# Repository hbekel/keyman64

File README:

Keyman64

Programmable C64 keyboard interceptor and hardware control system

The keyman64 is a programmable keyboard interceptor and hardware
control system for computers equipped with a simple 64-key matrix
keyboard.

It is installed between the keyboard and the computer, continually
scanning the keyboard matrix and relaying the keyboard state to the
computer using a crosspoint switch. To the computer, the crosspoint
switch matrix looks just like a physical keyboard, while the keyman64
gains the ability to intercept keystrokes and control the matrix seen
by the computer.

The keyman64 can be configured to intercept special key combinations
and invoke arbitrary sequences of commands to alter the state of
sixteen general purpose control lines provided on the board. These
lines can be used to control additional hardware instead of using
physical buttons or switches.

Additional features include the ability to send predefined keyboard
macros or to redefine the keyboard layout. Commands can also be sent
from a remote PC via USB, or send on simple serial wire interface,
allowing remote control from either a PC or another microcontroller or
similar device.

For some concrete examples of what the keyman64 can do, see the

http://www.henning-bekel.de/keyman64/#configuration-examples

Please refer to the project page http://www.henning-bekel.de/keyman64
for detailed documentation.

Copyright 2016 Henning Bekel <h.bekel@googlemail.com>

LICENSING

Hardware licenced under CERN OHL v.1.2, see ./hardware/LICENSE.txt
Software and firmware licenced under GNU GPLv3, see ./LICENSE

The software contains MIT licensed code from
https://github.com/arkku/ihex for reading Intel HEX files, Copyright
(c) 2013-2015 Kimmo Kulovesi, see ./intelhex/LICENSE

The firmware contains the V-USB Driver (https://www.obdev.at/vusb),
(C)2008 Objective Development GmbH.

Distributed in the ./bootloader directory is the USBasp bootloader,
(C)2013 Stephan Baerwolf (matrixstorm@gmx.de) and (C)2008 Objective
Development GmbH (https://www.obdev.at/vusb).

In compliance with the terms of the (identical) V-USB driver and
USBasp bootloader licenses (./firmware/usbdrv/License.txt and
./bootloader/License.txt), the entire project is published under

http://www.henning-bekel.de/keyman64

In addition, this distribution contains

- a circuit diagram in PDF format, see ./hardware/keyman64-schematics.pdf
- the full source code for the host software in ./firmware
- this README file
- references to https://www.obdev.at/vusb

The USB Product and Vendor IDs for the Keyman64 USB device have kindly
been provided by OpenMoko, Inc (http://openmoko.org).

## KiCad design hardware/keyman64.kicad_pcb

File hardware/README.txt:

Keyman64 Rev.4 -- Keyboard interceptor and hardware controller
Copyright Henning Bekel 2016.
Licensed under CERN OSH v.1.2 (see LICENSE.pdf)

This directory contains hardware documentation (as defined by the
terms of the CERN OSH v.1.2) for the Keyman64, a programmable
keyboard interceptor and hardware controller for the Commodore
C64. For more information, please visit

http://www.henning-bekel.de/keyman64

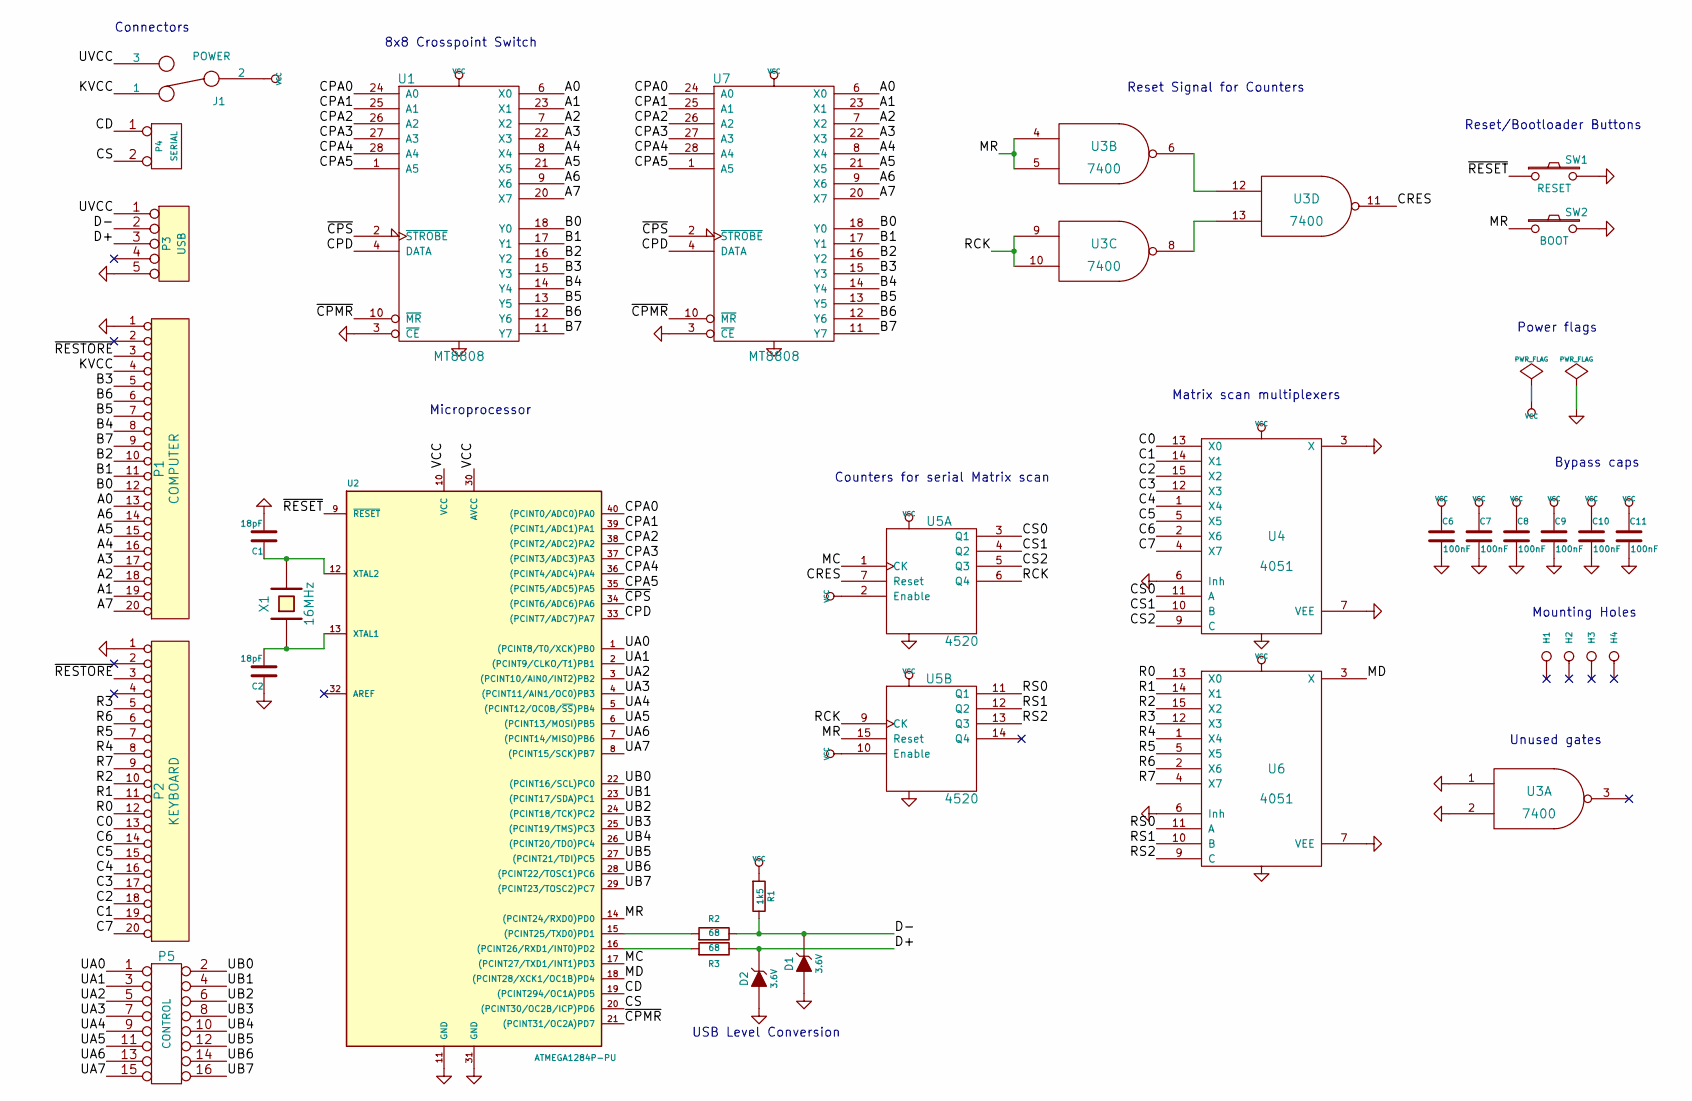
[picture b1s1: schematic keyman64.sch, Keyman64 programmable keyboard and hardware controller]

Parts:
C1, C2: 18pF; C_Disc_D3_P2.5
C6, C7, C8, C9, C10, C11: 100nF; C_Disc_D3_P2.5
D1, D2: 3.6V; D3
H1, H2, H3, H4: CONN_1; MountingHole_4mm
J1: POWER; pinHeader-3x1
P1: COMPUTER; pinHeader-20x1
P2: KEYBOARD; pinHeader-20x1
P3: USB; USB-MINI-B-H
P4: SERIAL; pinHeader-2x1
P5: CONTROL; pin_array_8x2
R1: 1k5; R3
R2, R3: 68; R3
SW1: RESET; Button
SW2: BOOT; Button
U1: MT8808; DIP-28__600
U2: ATMEGA1284P-PU; DIP-40__600
U3: 7400; DIP-14__300
U4, U6: 4051; DIP-16__300
U5: 4520; DIP-16__300
U7: MT8808; PLCC28
X1: 16MHz; HC-49V

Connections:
/A0: P1.13, U1.6 (X0), U7.6 (X0)
/A1: P1.19, U1.23 (X1), U7.23 (X1)
/A2: P1.18, U1.7 (X2), U7.7 (X2)
/A3: P1.17, U1.22 (X3), U7.22 (X3)
/A4: P1.16, U1.8 (X4), U7.8 (X4)
/A5: P1.15, U1.21 (X5), U7.21 (X5)
/A6: P1.14, U1.9 (X6), U7.9 (X6)
/A7: P1.20, U1.20 (X7), U7.20 (X7)
/B0: P1.12, U1.18 (Y0), U7.18 (Y0)
/B1: P1.11, U1.17 (Y1), U7.17 (Y1)
/B2: P1.10, U1.16 (Y2), U7.16 (Y2)
/B3: P1.5, U1.15 (Y3), U7.15 (Y3)
/B4: P1.8, U1.14 (Y4), U7.14 (Y4)
/B5: P1.7, U1.13 (Y5), U7.13 (Y5)
/B6: P1.6, U1.12 (Y6), U7.12 (Y6)
/B7: P1.9, U1.11 (Y7), U7.11 (Y7)
/C0: P2.13, U4.13 (X0)
/C1: P2.19, U4.14 (X1)
/C2: P2.18, U4.15 (X2)
/C3: P2.17, U4.12 (X3)
/C4: P2.16, U4.1 (X4)
/C5: P2.15, U4.5 (X5)
/C6: P2.14, U4.2 (X6)
/C7: P2.20, U4.4 (X7)
/CD: P4.1, U2.19 ((PCINT294/OC1A)PD5)
/CPA0: U1.24 (A0), U2.40 ((PCINT0/ADC0)PA0), U7.24 (A0)
/CPA1: U1.25 (A1), U2.39 ((PCINT1/ADC1)PA1), U7.25 (A1)
/CPA2: U1.26 (A2), U2.38 ((PCINT2/ADC2)PA2), U7.26 (A2)
/CPA3: U1.27 (A3), U2.37 ((PCINT3/ADC3)PA3), U7.27 (A3)
/CPA4: U1.28 (A4), U2.36 ((PCINT4/ADC4)PA4), U7.28 (A4)
/CPA5: U1.1 (A5), U2.35 ((PCINT5/ADC5)PA5), U7.1 (A5)
/CPD: U1.4 (DATA), U2.33 ((PCINT7/ADC7)PA7), U7.4 (DATA)
/CRES: U3.11, U5.7 (Reset)
/CS: P4.2 (PM), U2.20 ((PCINT30/OC2B/ICP)PD6)
/CS0: U4.11 (A), U5.3 (Q1)
/CS1: U4.10 (B), U5.4 (Q2)
/CS2: U4.9 (C), U5.5 (Q3)
/D+: D2.1 (K), P3.3, R3.1
/D-: D1.1 (K), P3.2, R1.1, R2.1
/KVCC: J1.1, P1.4
/MC: U2.17 ((PCINT27/TXD1/INT1)PD3), U5.1 (CK)
/MD: U2.18 ((PCINT28/XCK1/OC1B)PD4), U6.3 (X)
/MR: SW2.1, U2.14 ((PCINT24/RXD0)PD0), U3.4, U3.5, U5.15 (Reset)
/R0: P2.12, U6.13 (X0)
/R1: P2.11, U6.14 (X1)
/R2: P2.10, U6.15 (X2)
/R3: P2.5, U6.12 (X3)
/R4: P2.8, U6.1 (X4)
/R5: P2.7, U6.5 (X5)
/R6: P2.6, U6.2 (X6)
/R7: P2.9, U6.4 (X7)
/RCK: U3.9, U3.10, U5.6 (Q4), U5.9 (CK)
/RS0: U5.11 (Q1), U6.11 (A)
/RS1: U5.12 (Q2), U6.10 (B)
/RS2: U5.13 (Q3), U6.9 (C)
/UA0: P5.1, U2.1 ((PCINT8/T0/XCK)PB0)
/UA1: P5.3, U2.2 ((PCINT9/CLKO/T1)PB1)
/UA2: P5.5, U2.3 ((PCINT10/AIN0/INT2)PB2)
/UA3: P5.7, U2.4 ((PCINT11/AIN1/OC0)PB3)
/UA4: P5.9, U2.5 ((PCINT12/OC0B/~SS~)PB4)
/UA5: P5.11, U2.6 ((PCINT13/MOSI)PB5)
/UA6: P5.13, U2.7 ((PCINT14/MISO)PB6)
/UA7: P5.15, U2.8 ((PCINT15/SCK)PB7)
/UB0: P5.2, U2.22 ((PCINT16/SCL)PC0)
/UB1: P5.4, U2.23 ((PCINT17/SDA)PC1)
/UB2: P5.6, U2.24 ((PCINT18/TCK)PC2)
/UB3: P5.8, U2.25 ((PCINT19/TMS)PC3)
/UB4: P5.10, U2.26 ((PCINT20/TDO)PC4)
/UB5: P5.12, U2.27 ((PCINT21/TDI)PC5)
/UB6: P5.14, U2.28 ((PCINT22/TOSC1)PC6)
/UB7: P5.16, U2.29 ((PCINT23/TOSC2)PC7)
/UVCC: J1.3, P3.1
/~CPMR: U1.10 (~MR), U2.21 ((PCINT31/OC2A)PD7), U7.10 (~MR)
/~CPS: U1.2 (~STROBE), U2.34 ((PCINT6/ADC6)PA6), U7.2 (~STROBE)
/~RESET: SW1.1, U2.9 (~RESET)
/~RESTORE: P1.3, P2.3
GND: C1.2, C2.1, C6.2, C7.2, C8.2, C9.2, C10.2, C11.2, D1.2 (A), D2.2 (A), P1.1, P2.1, P3.5, SW1.2, SW2.2, U1.3 (~CE), U1.5 (VSS), U2.11 (GND), U2.31 (GND), U3.1, U3.2, U3.7 (GND), U4.3 (X), U4.6 (Inh), U4.7 (VEE), U4.8 (VSS), U5.8 (VSS), U6.6 (Inh), U6.7 (VEE), U6.8 (VSS), U7.3 (~CE), U7.5 (VSS)
unnamed: C1.1, U2.12 (XTAL2), X1.2
unnamed: C2.2, U2.13 (XTAL1), X1.1
unnamed: R2.2, U2.15 ((PCINT25/TXD0)PD1)
unnamed: R3.2, U2.16 ((PCINT26/RXD1/INT0)PD2)
unnamed: U3.6, U3.12
unnamed: U3.8, U3.13
VCC: C6.1, C7.1, C8.1, C9.1, C10.1, C11.1, J1.2, R1.2, U1.19 (VDD), U2.10 (VCC), U2.30 (AVCC), U3.14 (VCC), U4.16 (VDD), U5.2 (Enable), U5.10 (Enable), U5.16 (VDD), U6.16 (VDD), U7.19 (VDD)

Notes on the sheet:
USB Level Conversion
8x8 Crosspoint Switch
Reset Signal for Counters
Connectors
Counters for serial Matrix scan
Matrix scan multiplexers
Reset/Bootloader Buttons
Microprocessor
Unused gates
Power flags
Bypass caps
Mounting Holes

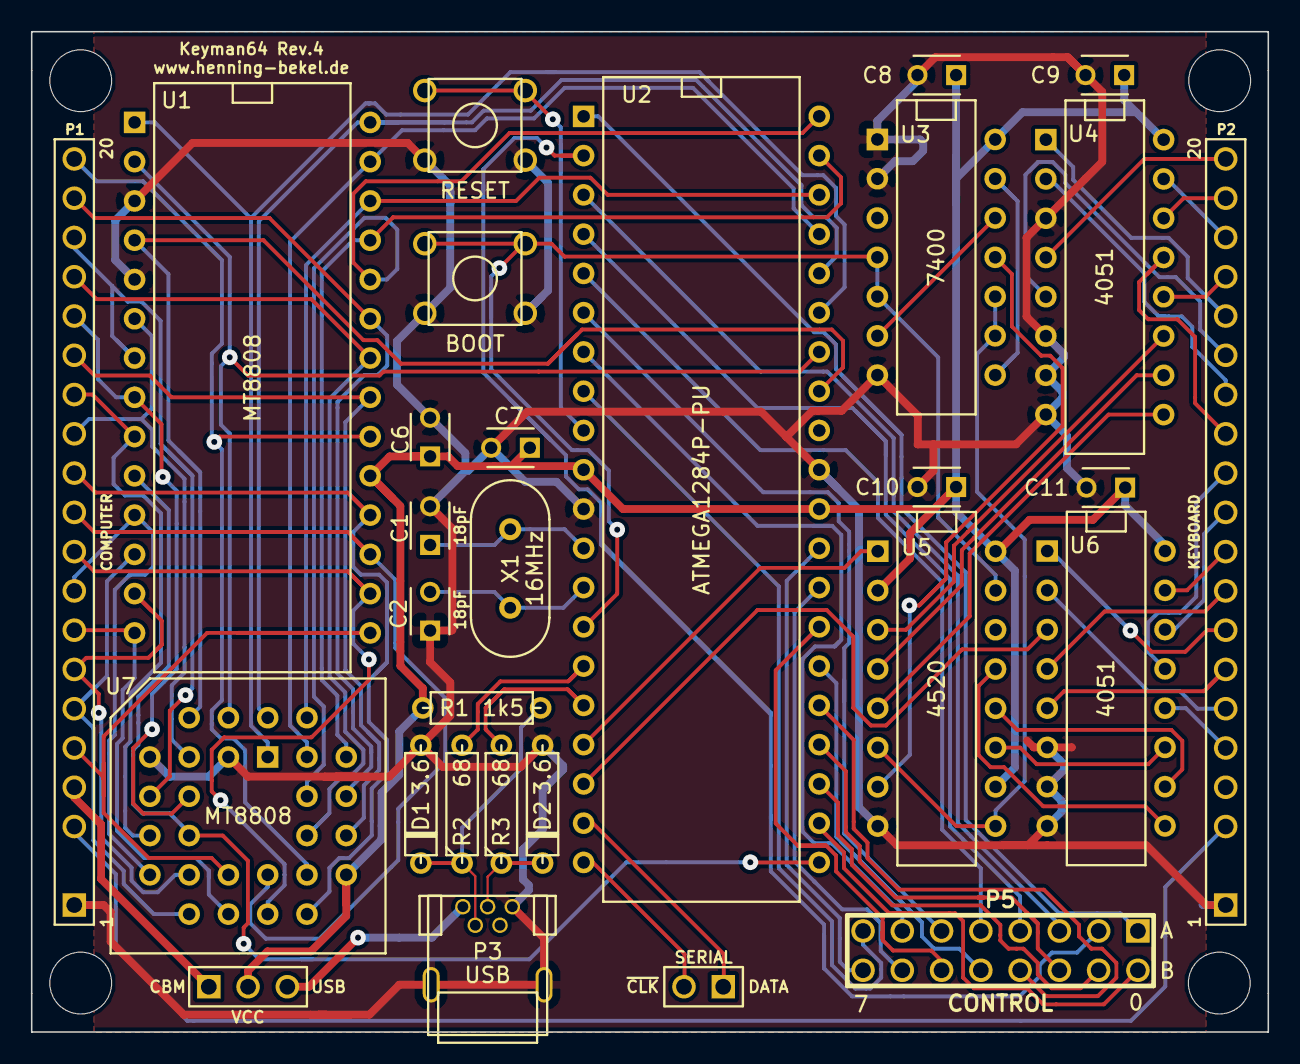
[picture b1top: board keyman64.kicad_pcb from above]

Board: 2 copper layers, 80.0 x 64.7 mm, 33 parts (0 on the bottom side), 84 nets.

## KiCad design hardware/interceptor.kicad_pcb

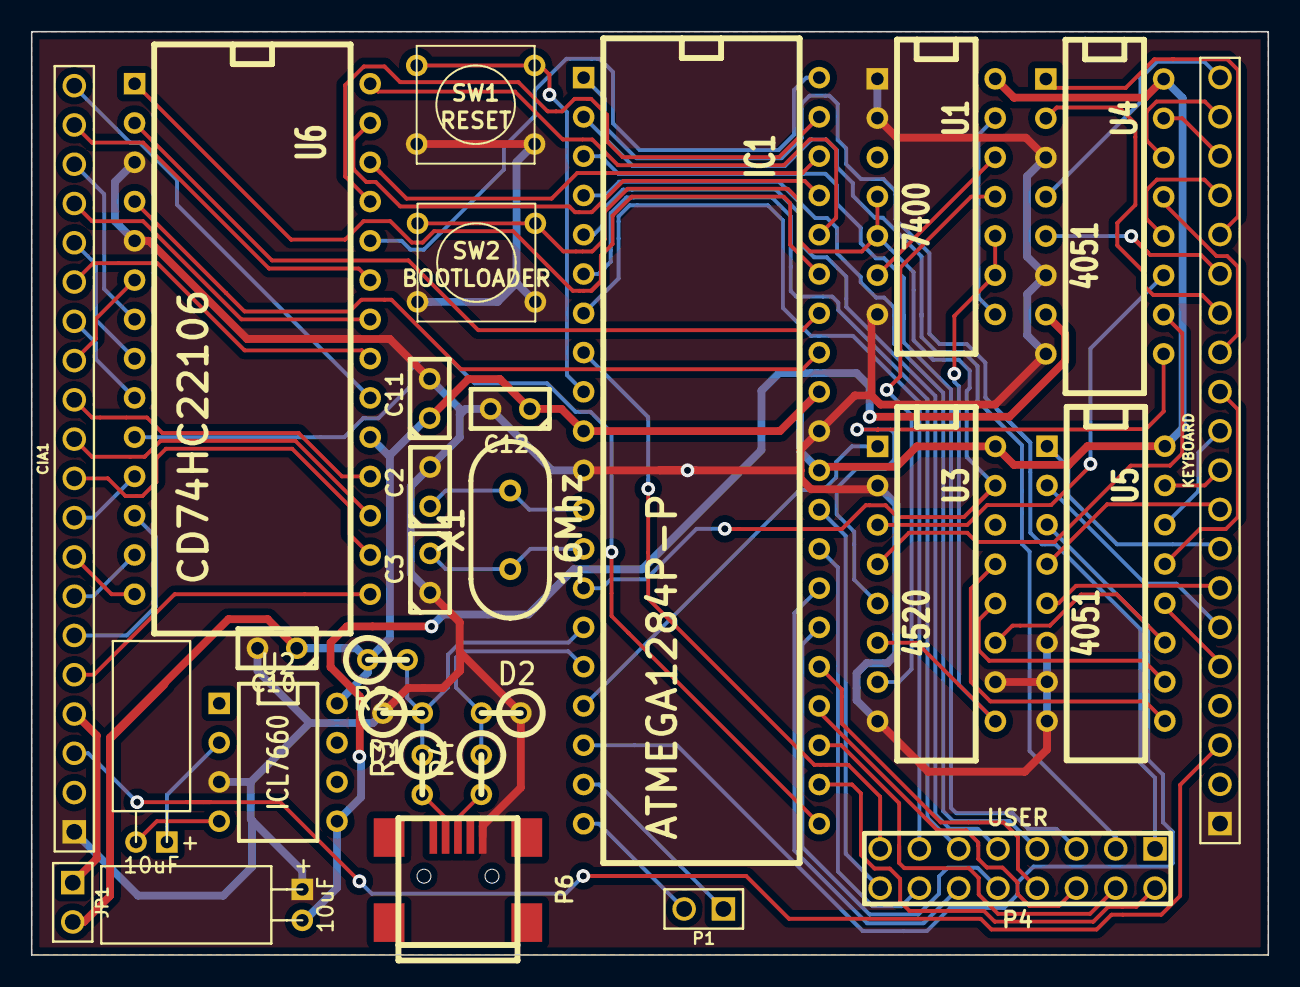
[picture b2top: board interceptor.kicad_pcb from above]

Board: 2 copper layers, 80.0 x 59.7 mm, 28 parts (0 on the bottom side), 86 nets.

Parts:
C2, C3: 18nF; C1
C4, C5: 10uF; CR2H11W5H
C10, C11, C12: 100nF; C1
D1, D2: 3.6V; R1
IC1: ATMEGA1284P-P; DIP-40__600
JP1: JUMPER; PIN_ARRAY_2X1
P1: TAPEPORT; PIN_ARRAY_2X1
P2: CIA1; pinHeader-20x1
P3: KEYBOARD; pinHeader-20x1
P4: USER; pin_array_8x2
P6: USB; USB_MINI_B_CORRECTED
R2: 1k5; R1
R3, R4: 68; R1
SW1: RESET; SW_PUSH_SMALL
SW2: BOOTLOADER; SW_PUSH_SMALL
U1: 7400; DIP-14__300
U2: ICL7660; DIP-8__300
U3: 4520; DIP-16__300
U4, U5: 4051; DIP-16__300
U6: CD74HC22106; DIP-28__600
X1: 16Mhz; HC-49V

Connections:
/A0: P2.13, U6.6
/A1: P2.19, U6.23
/A2: P2.18, U6.7
/A3: P2.17, U6.22
/A4: P2.16, U6.8
/A5: P2.15, U6.21
/A6: P2.14, U6.9
/A7: P2.20, U6.20
/B0: P2.12, U6.18
/B1: P2.11, U6.17
/B2: P2.10, U6.16
/B3: P2.5, U6.15
/B4: P2.8, U6.14
/B5: P2.7, U6.13
/B6: P2.6, U6.12
/B7: P2.9, U6.11
/C0: P3.13, U4.13
/C1: P3.19, U4.14
/C2: P3.18, U4.15
/C3: P3.17, U4.12
/C4: P3.16, U4.1
/C5: P3.15, U4.5
/C6: P3.14, U4.2
/C7: P3.20, U4.4
/CD: IC1.20, P1.2
/CPA0: IC1.40, U6.24
/CPA1: IC1.39, U6.25
/CPA2: IC1.38, U6.26
/CPA3: IC1.37, U6.27
/CPA4: IC1.36, U6.28
/CPA5: IC1.35, U6.1
/CPD: IC1.33, U6.4
/CRES: U1.11, U3.7
/CS: IC1.19, P1.1
/CS0: U3.3, U4.11
/CS1: U3.4, U4.10
/CS2: U3.5, U4.9
/D+: P6.3, R4.2
/D-: P6.2, R3.2
/EXTVCC: JP1.1, P2.4
/MC: IC1.17, U3.1
/MD: IC1.18, U5.3
/MR: IC1.14, SW2.1, U1.4, U1.5, U3.15
/R0: P3.12, U5.13
/R1: P3.11, U5.14
/R2: P3.10, U5.15
/R3: P3.5, U5.12
/R4: P3.8, U5.1
/R5: P3.7, U5.5
/R6: P3.6, U5.2
/R7: P3.9, U5.4
/RCK: U1.9, U1.10, U3.6, U3.9
/RS0: U3.11, U5.11
/RS1: U3.12, U5.10
/RS2: U3.13, U5.9
/UA0: IC1.1, P4.1
/UA1: IC1.2, P4.3
/UA2: IC1.3, P4.5
/UA3: IC1.4, P4.7
/UA4: IC1.5, P4.9
/UA5: IC1.6, P4.11
/UA6: IC1.7, P4.13
/UA7: IC1.8, P4.15
/UB0: IC1.22, P4.2
/UB1: IC1.23, P4.4
/UB2: IC1.24, P4.6
/UB3: IC1.25, P4.8
/UB4: IC1.26, P4.10
/UB5: IC1.27, P4.12
/UB6: IC1.28, P4.14
/UB7: IC1.29, P4.16
/VEE: C5.2, U2.5, U4.7
/~CPMR: IC1.21, U6.10
/~CPS: IC1.34, U6.2
/~RESET: IC1.9, SW1.1
/~RESTORE: P2.3, P3.3
GND: C2.2, C3.1, C5.1, C10.2, C11.2, C12.2, D1.1, D2.1, IC1.11, IC1.31, P2.1, P3.1, P6.5, SW1.2, SW2.2, U1.1, U1.2, U1.7, U2.3, U3.2, U3.8, U3.10, U4.3, U4.6, U4.8, U5.6, U5.7, U5.8, U6.3, U6.5
unnamed: C4.1, U2.2
unnamed: C4.2, U2.4
unnamed: C2.1, IC1.12, X1.2
unnamed: C3.2, IC1.13, X1.1
unnamed: D2.2, IC1.16, R4.1
unnamed: D1.2, IC1.15, R2.2, R3.1
unnamed: U1.6, U1.12
unnamed: U1.8, U1.13
VCC: C10.1, C11.1, C12.1, IC1.10, IC1.30, IC1.32, JP1.2, R2.1, U1.14, U2.8, U3.16, U4.16, U5.16, U6.19

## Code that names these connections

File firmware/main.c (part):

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#include "encoding.h"
#include "../protocol.h"

uint8_t MC = 1<<PD3; // Matrix Clock
uint8_t MD = 1<<PD4; // Matrix Data
uint8_t MR = 1<<PD0; // Matrix Counter Reset

uint8_t CPS = 1<<PA6; // Crosspoint Strobe
uint8_t CPD = 1<<PA7; // Crosspoint Data
uint8_t CPR = 1<<PD7; // Crosspoint Reset

uint8_t CLK   = 1<<PD6; // Serial Clock (active low)
uint8_t DATA  = 1<<PD5; // Serial Data

#define STATE_RELAY   0x00
#define STATE_COMMAND 0x01
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
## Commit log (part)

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2013-01-18 Firmware/Client: Implement slow/fast scanning, started implementing port expansion
2015-07-20 Added uart based printf debugging, rearranged atmega port layout
2015-07-25 Using pin change interrupts to relay matrix... no dice
2015-07-25 Hardware: Added USB Level Conversion Diodes and Resistors
2015-07-26 Firmware: Also use HWBE line as matrix reset line, reset before each scan
2015-07-26 Started implementing state machine and key handling for command key
2015-07-27 Added toplevel Makefile
2015-07-27 Grounded crosspoint enable, connected master reset to uC
    Master Reset line is more suitable to make the matrix "float"
2015-07-27 Fixed tristate command, set pin to input *without* pullup
2015-07-28 Refactored binding execution, added execute command
2015-07-28 Removed Userport initialization (already done when applying config)
2015-07-29 Software: Started implementing configuration file parsing
    TODO:
    - Refactor Read* functions creating config from binary format
    - Add Write* functions creating binary data from config structs
    - Add individual print functions for config structs
    - Add symbolic key names
    - Allow using binary values prefixed with %
2015-07-29 Software: Minor changes in control.asm
2015-07-30 Hardware: Added first draft of pcb layout with simple autorouting
2015-07-31 Software: Improved test target, removed unused code
2015-08-03 Hardware: Fixed Crosspoint switch and usb connector, routed usb traces
2015-08-03 Hardware: First serious draft of pcb layout
2015-08-12 Software: Changed meta key to work as a modifier key
    As long as the meta key is held down, the software listens for and
    executes key bindings. The key is relayed on release if no bound key
    was pressed in the meantime.
    This avoids having to press the meta key twice in order to actually
    type it. The only difference to other keys is that the character does
    not appear immediately on key down but on release. This also makes
2015-08-12 Firmware: Fixed bug in QueryKeyUp() function
2015-08-13 Software/Firmware: Allow defining the meta key using the new "meta" command
    If no meta key is defined with a meta command, arrow-left is used
    by default.
2015-08-15 Makefile: Added install/uninstall targets
2015-08-18 Software: Makefile: Allow using alternative c-compiler
2015-08-18 Software: Use symbolic names (ZERO..NINE) for keys 0..9
    This simplifies parsing by eliminating ambiguities
    (key "1" vs value 1).
2015-08-18 Hardware: Improved routing around the edge connectors
2015-08-30 Software: Added simple test program for reverse keyboard scan
    Here Port B is set to output and Port A is set to input, which is the
    reverse of how the kernal keyscan routine usually does it.
    Proves that the 7422106 has truly bidirectional switches (not stated
    explicitly in the datasheet).
2015-09-05 Software/Firmware: Simplified key encoding (numbered from 0-63)
    Instead of encoding the row/columns in the high and low nibbles, we now
    simply number the keys in a linear fashion corresponding to their position
    in the matrix (starting from the top left at 0:0 downto 7:7).
    This greatly simplifies the code and creates a direct correlation of key
    symbols to the addresses used for the crosspoint switch.
2015-09-07 Firmware: Added "boot" command to enter the firmware from software
2015-09-13 Software/Firmware: Allow to sleep for up to 65535 milliseconds
2015-09-14 Firmware: Code cleanup (no magic numbers for encoduing key action)
2015-09-14 Firmware: Fixed serial commands for key down and key up
    When a key is held down via the serial interface, it will remain down
    until it is released via the serial interface up command. The respective
    respective key is locked while it is down, meaning the state of the
    physical keyboard key is excluded from being permanently relayed to the
    crosspoint switch matrix facing the C64.
2015-09-16 Software: Avoid adding identical strings twice to the binary configuaration
2015-09-21 Deleted TODO list
2015-09-25 Software/Firmware: Allow configuring crosspoint switch model at runtime
    This avoids having to build/ship different versions of the firmware
    for the crosspoint switch IC model in use.
    The configuration command 'using' has been added for this purpose:
    using CD74HC22106
    using MT8808
    The default model is CD74HC22106 to maintain backwards compatibility.
2015-10-01 Firmware/Makefile: Removed useless avrdude port option in "program" target
2015-10-14 Hardware: Rev.2, Increased VIA sizes, Added alternative VCC pin header
2015-10-16 Hardware: Added mounting hole module
2015-10-17 Firmware: Added support for executing bindings via USB
2015-10-18 Firmware/Software: Redesigned to execute any command via USB
    The device now implements a low speed usb device implementing a remote
    control interface during regular opertion.
    The semantics of the keyman64 commandline utitlity have been changed
    to allow the execution of arbitrary commands passed on the commandline
    or on stdin via USB, e.g.:
    $ keyman64 exec k
2015-10-24 Hardware: Increased board height to 6,4cm to make room for mounting holes
2015-10-27 Software: Properly create temp filename for fmemopen() on win32
2015-10-28 Hardware: Improved routing, assured ground connections, fixed silkscreen
2015-11-04 Hardware: Revision 2
    Updated svg renderings, fixed some more file modes
2015-11-16 Hardware: Improved silkscreen, routing
2015-11-18 Hardware: Use single switch component for power jumper instead of double
2015-11-19 Hardware: Revision 2 final version
2015-11-23 Hardware: Updated renderings of schematics and placment
2015-11-25 Makefile: Added udev rules, install/uninstall when uname is Linux
2015-12-07 Software: Adjusted udev rule to use new vid/pid
2016-01-19 Firmware/Software: Added save and restore commands
    These commands save or restore the state of all control lines.
2016-01-21 Firmware/Software: Allow executing different commands every other time
    It is now possible to specify an execution policy for commands that controls
    whether a command is always executed each time a binding is triggered or
    only every other time (even or odd):
    <key>:[<policy>] <command>
    Where policy is either "0" or "1" for even or odd. If no policy is given,
    the default is to always execute the command (like before). For example:
2016-01-22 Makefile: Worked around broken firmware clean target on cygwin
    The clean target of the firmware makefile accidently deletes usbdrvasm.S
    under cygwin due to the case insensitivity of filenames on windows.
2016-03-16 Hardware: Increased mounting hole size to 4mm
    This was self-adhesive pcb holders like reichelts AHS 4,8 may be used
2016-04-19 Hardware: Improved routing, silkscreen
2016-05-04 Hardware: Moved USB components slightly to the right
2016-05-31 Version 1.2
    Changes in this version:
    Hardware:
    * Updated to board revision 3
    * Removed obsolete negative power supply ICL7660 and caps
    * Disconnected AREF pin on Atmel as recommended in datasheet
    * Added alternative PLCC28 socket for the crosspoint switch
2016-06-03 Firmware: Added Test command to fallback configuration (<meta>-t)
2016-07-25 Hardware: Fixed wrong USB level conversion circuit
2016-08-16 Hardware: Improved routing at ground pads (thermal properties)
2016-08-16 Hardware: Improved routing, copper fills
2016-08-22 Hardware: Moved serial header to align with vcc jumper, improved silkscreen
2016-09-19 Firmware: Fixed bug in encoding.h
    Ascii underscore did not correctly map to petscii
    left-arrow but the backtick did.
2016-09-21 Makefile: Removed explicit use of dash leftover from testing
2016-09-24 Firmware: Reset crosspoint switch before running initial commands
    Didn't initialise the crosspoint switch before running initial commands,
    which caused the INST/DEL key to be held down until the initial
    commands were finished. This was only noticeable when the initial
    sequence contained a long running command involving some delays.
    Also it seems that at least the MT8808 needs a manual reset as well.
    Need to investigate, workaround for now.
2016-10-20 Software: Also show decimal values for keys (keyman64 --keys)
2016-11-04 Project: Added license texts, added schematics in pdf format
2016-11-08 Software: Sanitized PETSCII encoding, proper escape sequences
    The string literal syntax for the "type" command has
    been corrected and completed. It is now possible for
    the keyman to type everything that can be typed on a
    real C64 keyboard.
    The previous scheme of incorrectly using the ascii tilde,
    pipe and backtick for control codes has been removed,
2016-11-09 Makefile: Fixed config target, added a simple example.conf
2016-11-27 Software: Trim value part of symbol definitions
    Fixes a bug that would leave trailing whitespace in symbol values
    when adding a comment to the line after the value part.
2016-12-21 Hardware: Added button models for 3d view
2017-01-18 Firmware: Some bugfixes solving INST/DEL bounce problems
2017-01-23 Firmware: Return accepts password, prevent setting empty password
    When locked, the password is now accepted by pressing return, i.e.
    return is implicitly added to passwords.
    The password command is now cancelled when an empty password
    is entered.
2017-01-26 Firmware: Allow clearing the password, disabling locks
    When an empty password is entered, the password is now cleared again
    and lock commands will abort with the appropriate message.
    Also some changes to the type function and calls under the hood.
2017-02-26 Makefile: Patch binary firmware image to 128kb with 0xff
    This is only because the linux minipro client accepts images
    in progmem size only.
2017-04-13 Firmware: Added early scan and relay step on powerup
    Added an early one-time keyboard scan and relay step
    before entering USB initialisation to allow any
    extension port modules which do an early keyboard scan
    in their reset routine to work properly at powerup.
    E.g. an Action Replay cartridge will enter right
    into direct mode with fastload enabled if C= is held
2017-04-19 Software: Fixed bug in symbol parsing, added test case
    Any line containing an equals sign was interpreted
    as a symbol definition, which failed for type commands
    containing an equal signs.
    Reported by Sven Arke
2017-04-30 Software: Cleaned up basic loader example
2017-05-04 Project: Added Makefile.inc defining current version
2017-06-19 Firmware/Software: Implemented port expansion support
    It is now possible to expand the number of control pins
    by using one or more (daisy chained) 74HC595 shift
    registers. Only four native control pins are required to
    drive the shift registers. The new configuration directive
    "expand" can be used to specify the number of additional
    registers and the pins used to control the shift register
2017-07-07 Software: Improved configuration syntax for "expand" directive
2017-07-23 Software/Firmware: Refactored and simplified handling of State/Storage
2017-07-24 Firmware: Allow for multiple mappings to the same key
2017-07-27 Software/Firmware: Added proper reset command, removed --reset again
    Added proper keyman reset command, removed the --reset option again.
    The "reset" command can be bound to a key, however when invoking
    "keyman64 reset" remotely, the device will still be reset directly
    via USB, regardless of wether the device is in bootloader or
    application mode.
2017-09-10 Added a proper Changelog documenting all previous changes
2022-09-11 Software: Minor code cleanup
2023-04-23 Firmware: Removed build date from version string
2023-04-24 Makefile: Generate win32 msi using msitools, added to release target
2023-04-26 Software/Firmware: Added command 'serial' to set USB serial number
    A new configuration command 'serial' has been added that allows setting
    the USB serial number string. Maximum length for the string is 16
    characters. If no 'serial' command is issued at startup, the serial number
    defaults to the empty string.
    This allows the user to configure persistent device symlinks for multiple
    keyman64 devices under linux by using appropriate udev rules that take

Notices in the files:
hardware/keyman64.kicad_pcb:
This documentation describes Open Hardware and is licensed under the CERN OHL v. 1.2.\
You may redistribute and modify this documentation under the terms of the CERN OHL v.1.2.\
